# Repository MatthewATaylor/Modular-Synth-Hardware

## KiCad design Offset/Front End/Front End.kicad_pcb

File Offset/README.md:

# Offset

Two DC offsets, each applied to six output channels.

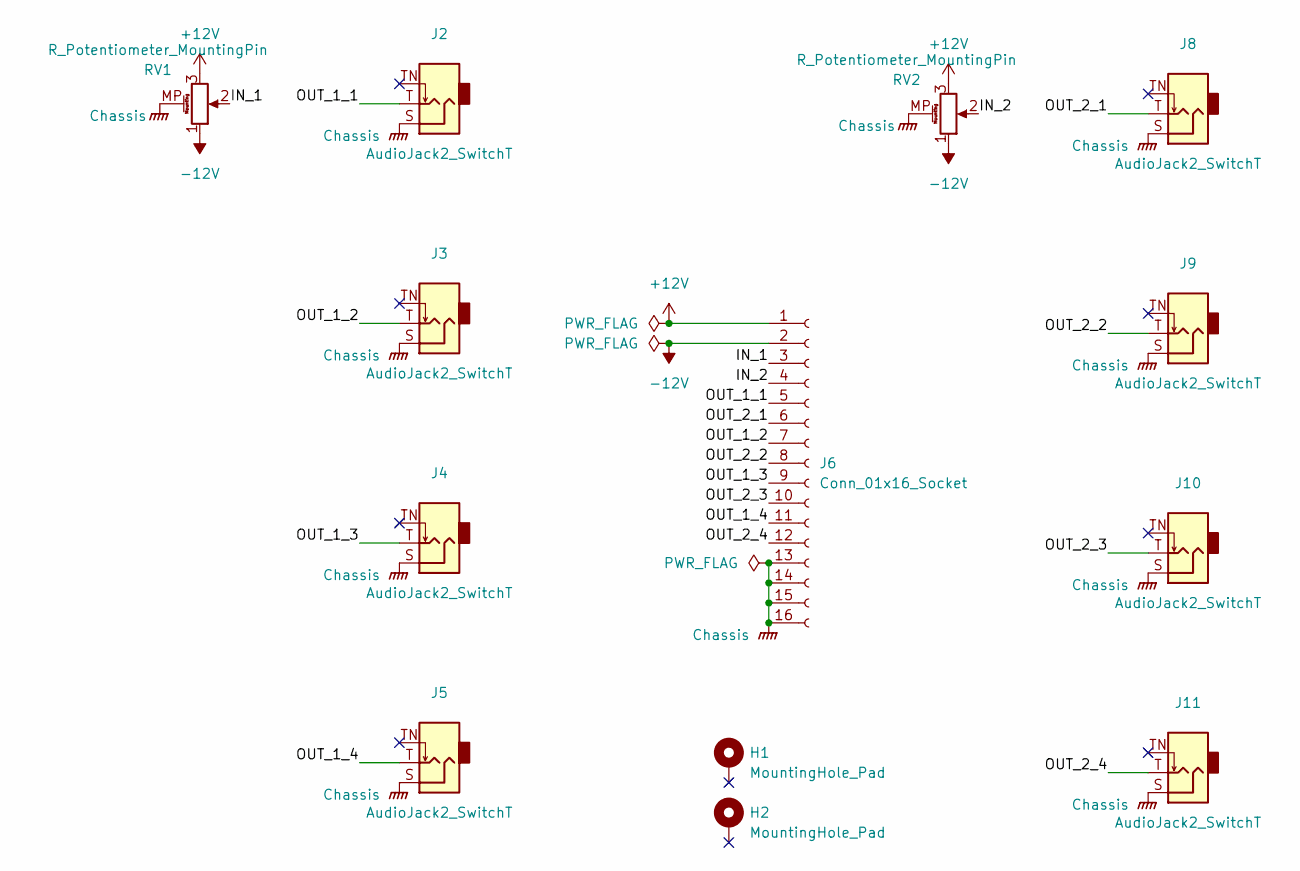
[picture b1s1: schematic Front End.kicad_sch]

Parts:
H1, H2: MountingHole_Pad; MountingHole_Pitch7.5mm_Drill3.4mm
J2, J3, J4, J5, J8, J9, J10, J11: AudioJack2_SwitchT; Jack_3.5mm_QingPu_WQP-PJ398SM_Vertical_CircularHoles
J6: Conn_01x16_Socket; PinSocket_1x16_P2.54mm_Vertical
RV1, RV2: R_Potentiometer_MountingPin; Potentiometer_Alpha_RD901F-40-00D_Single_Vertical_MP

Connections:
+12V: J6.1, RV1.3, RV2.3
-12V: J6.2, RV1.1, RV2.1
/IN_1: J6.3, RV1.2
/IN_2: J6.4, RV2.2
/OUT_1_1: J2.T, J6.5
/OUT_1_2: J3.T, J6.7
/OUT_1_3: J4.T, J6.9
/OUT_1_4: J5.T, J6.11
/OUT_2_1: J6.6, J8.T
/OUT_2_2: J6.8, J9.T
/OUT_2_3: J6.10, J10.T
/OUT_2_4: J6.12, J11.T
Chassis: J2.S, J3.S, J4.S, J5.S, J6.13, J6.14, J6.15, J6.16, J8.S, J9.S, J10.S, J11.S, RV1.MP (MountPin), RV2.MP (MountPin)

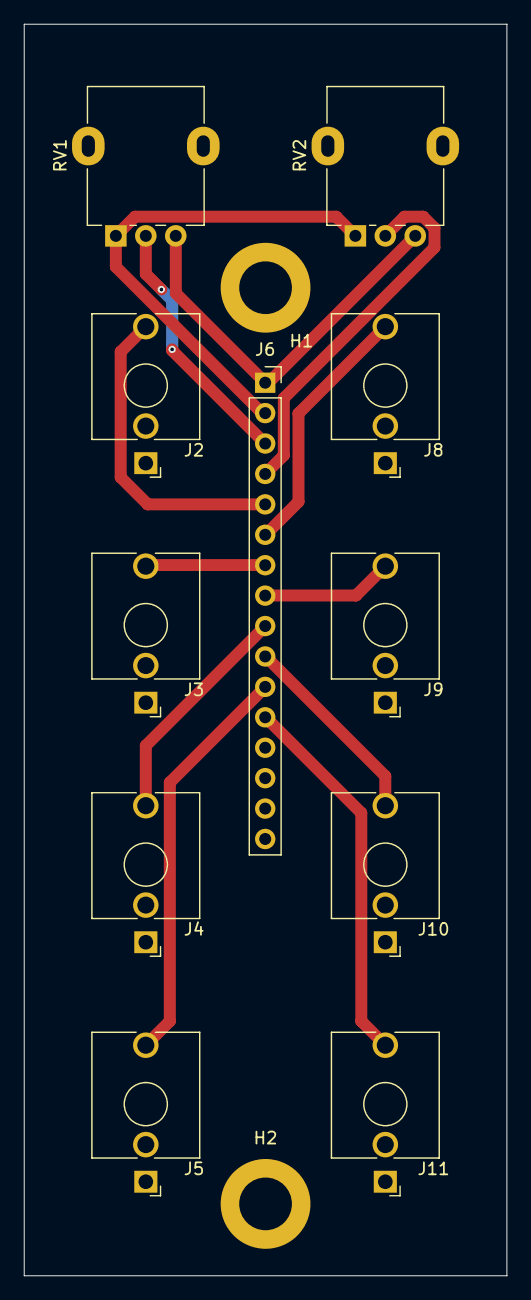
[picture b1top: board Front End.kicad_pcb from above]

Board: 2 copper layers, 40.3 x 104.5 mm, 13 parts (0 on the bottom side), 13 nets.

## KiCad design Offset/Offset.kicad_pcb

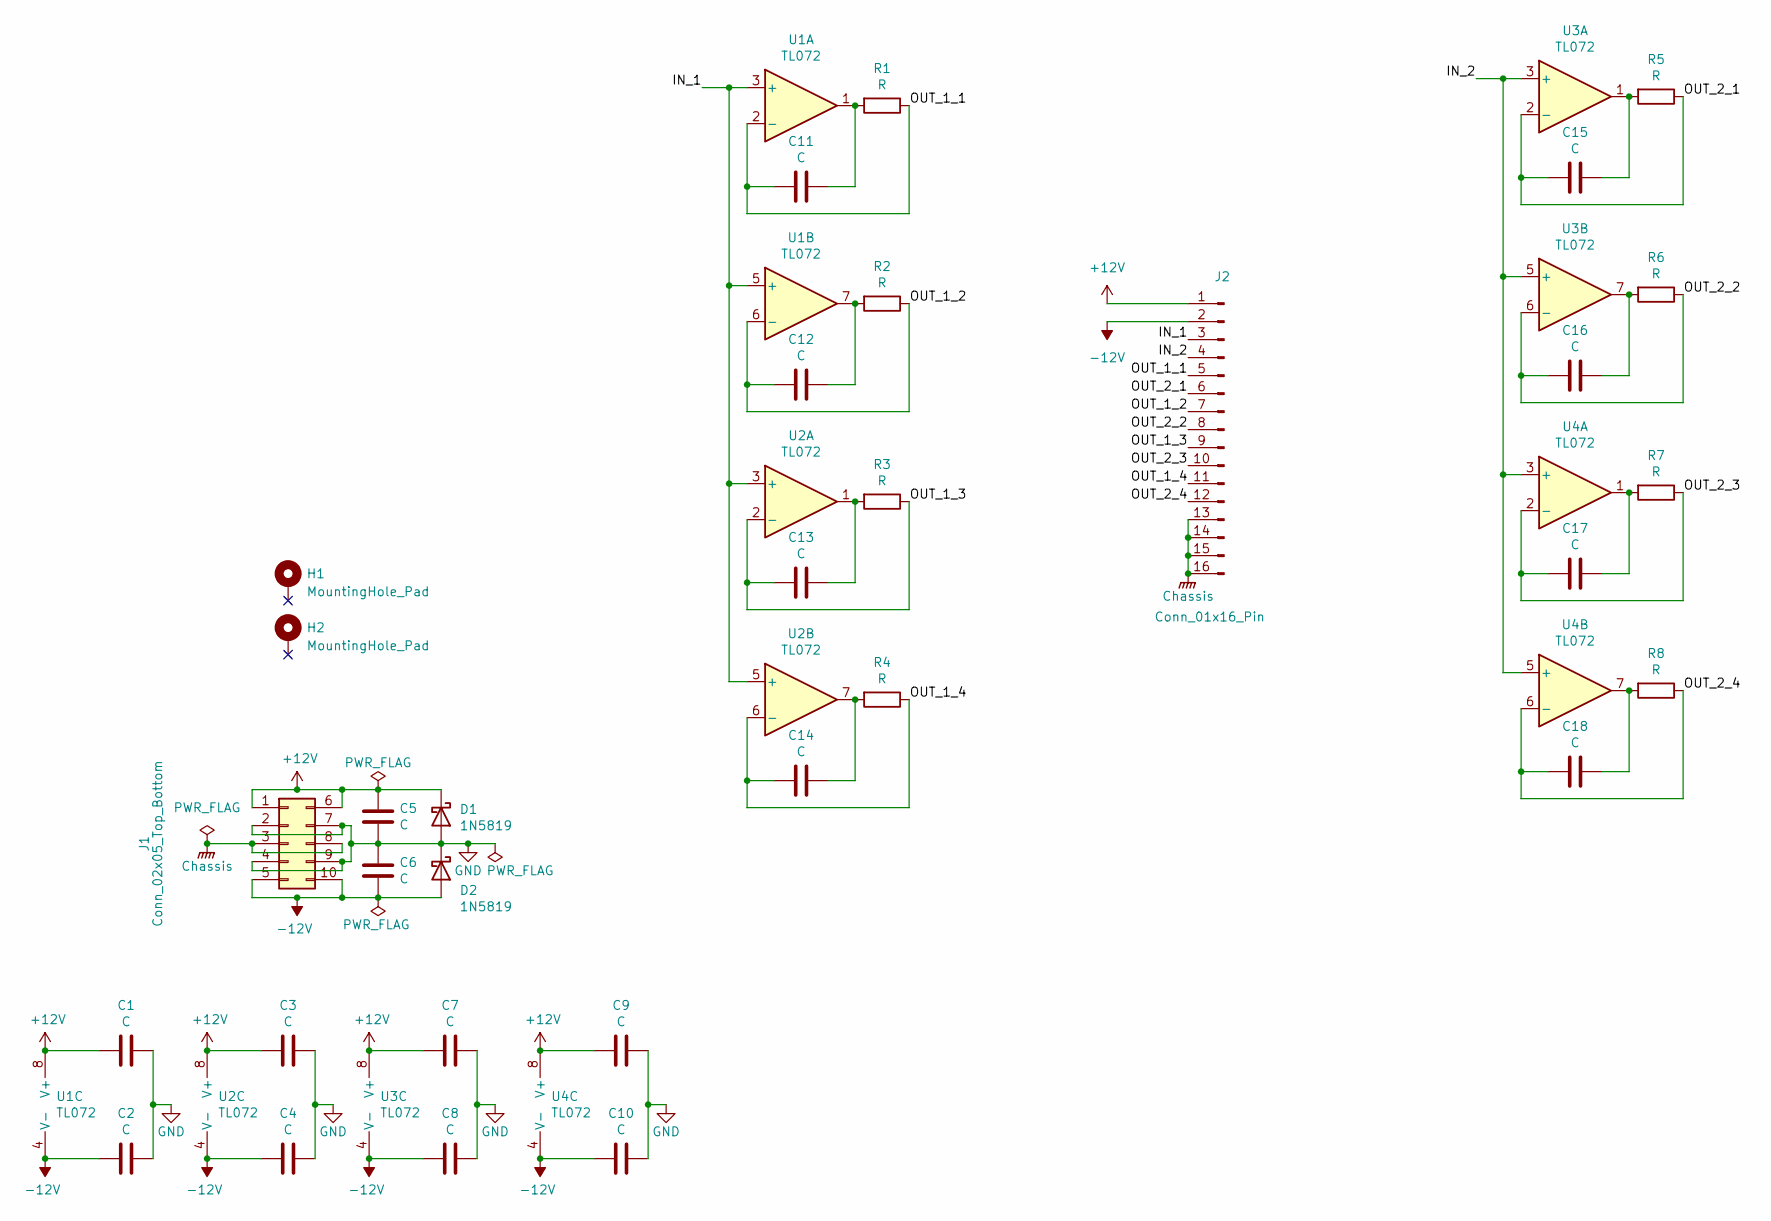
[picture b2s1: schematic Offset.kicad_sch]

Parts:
C1, C2, C3, C4, C7, C8, C9, C10, C11, C12, C13, C14, C15, C16, C17, C18: C; C_Disc_D5.5mm_W2.5mm_P2.50mm
C5, C6: C; C_Disc_D5.5mm_W4.0mm_P2.50mm
D1, D2: 1N5819; D_DO-41_SOD81_P10.16mm_Horizontal
H1, H2: MountingHole_Pad; MountingHole_Pitch7.5mm_Drill3.4mm
J1: Conn_02x05_Top_Bottom; Molex_Mini-Fit_Jr_5566-10A_2x05_P4.20mm_Vertical
J2: Conn_01x16_Pin; PinHeader_1x16_P2.54mm_Vertical
R1, R2, R3, R4, R5, R6, R7, R8: R; R_Axial_DIN0207_L6.3mm_D2.5mm_P7.62mm_Horizontal
U1, U2, U3, U4: TL072; DIP-8_W7.62mm_Socket

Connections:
+12V: C1.1, C3.1, C5.1, C7.1, C9.1, D1.1 (K), J1.1, J1.6, J2.1, U1.8 (V+), U2.8 (V+), U3.8 (V+), U4.8 (V+)
-12V: C2.1, C4.1, C6.2, C8.1, C10.1, D2.2 (A), J1.5, J1.10, J2.2, U1.4 (V-), U2.4 (V-), U3.4 (V-), U4.4 (V-)
/IN_1: J2.3, U1.3 (+), U1.5 (+), U2.3 (+), U2.5 (+)
/IN_2: J2.4, U3.3 (+), U3.5 (+), U4.3 (+), U4.5 (+)
/OUT_1_1: C11.1, J2.5, R1.1, U1.2 (-)
/OUT_1_2: C12.1, J2.7, R2.1, U1.6 (-)
/OUT_1_3: C13.1, J2.9, R3.1, U2.2 (-)
/OUT_1_4: C14.1, J2.11, R4.1, U2.6 (-)
/OUT_2_1: C15.1, J2.6, R5.1, U3.2 (-)
/OUT_2_2: C16.1, J2.8, R6.1, U3.6 (-)
/OUT_2_3: C17.1, J2.10, R7.1, U4.2 (-)
/OUT_2_4: C18.1, J2.12, R8.1, U4.6 (-)
Chassis: J1.3, J1.8, J2.13, J2.14, J2.15, J2.16
GND: C1.2, C2.2, C3.2, C4.2, C5.2, C6.1, C7.2, C8.2, C9.2, C10.2, D1.2 (A), D2.1 (K), J1.2, J1.4, J1.7, J1.9
unnamed: C11.2, R1.2, U1.1
unnamed: C12.2, R2.2, U1.7
unnamed: C13.2, R3.2, U2.1
unnamed: C14.2, R4.2, U2.7
unnamed: C15.2, R5.2, U3.1
unnamed: C16.2, R6.2, U3.7
unnamed: C17.2, R7.2, U4.1
unnamed: C18.2, R8.2, U4.7

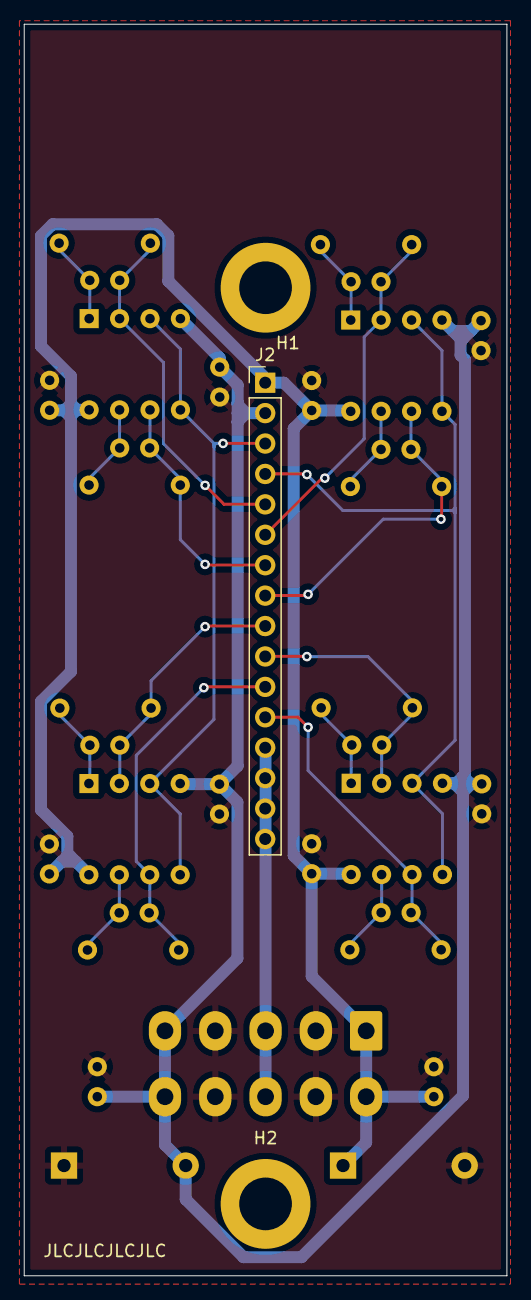
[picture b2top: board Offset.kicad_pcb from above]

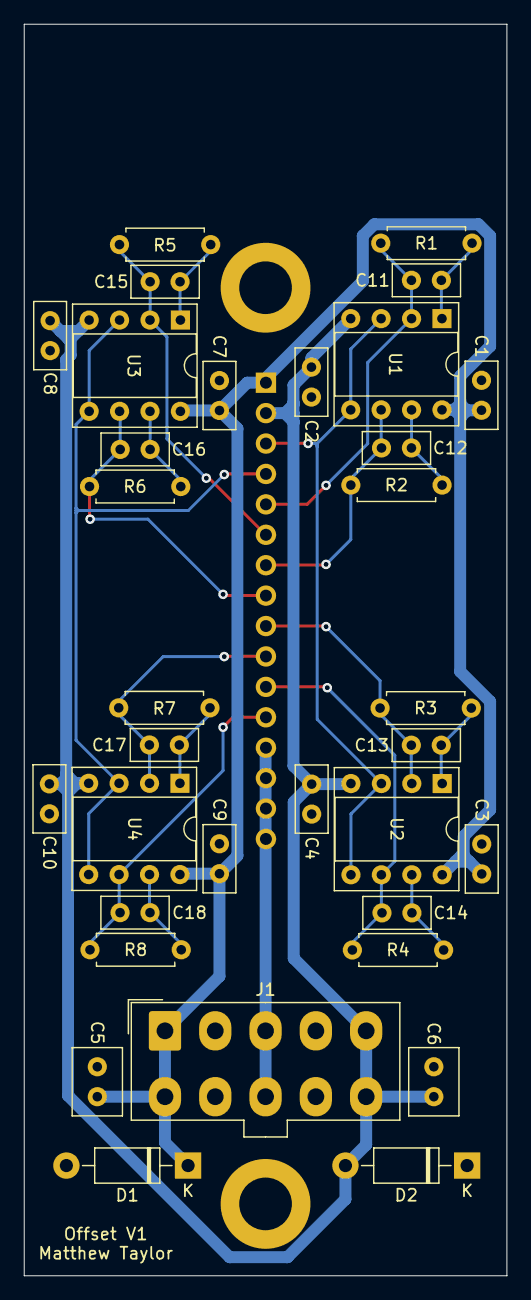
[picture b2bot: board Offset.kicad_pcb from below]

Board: 2 copper layers, 40.3 x 104.5 mm, 36 parts (33 on the bottom side), 22 nets.

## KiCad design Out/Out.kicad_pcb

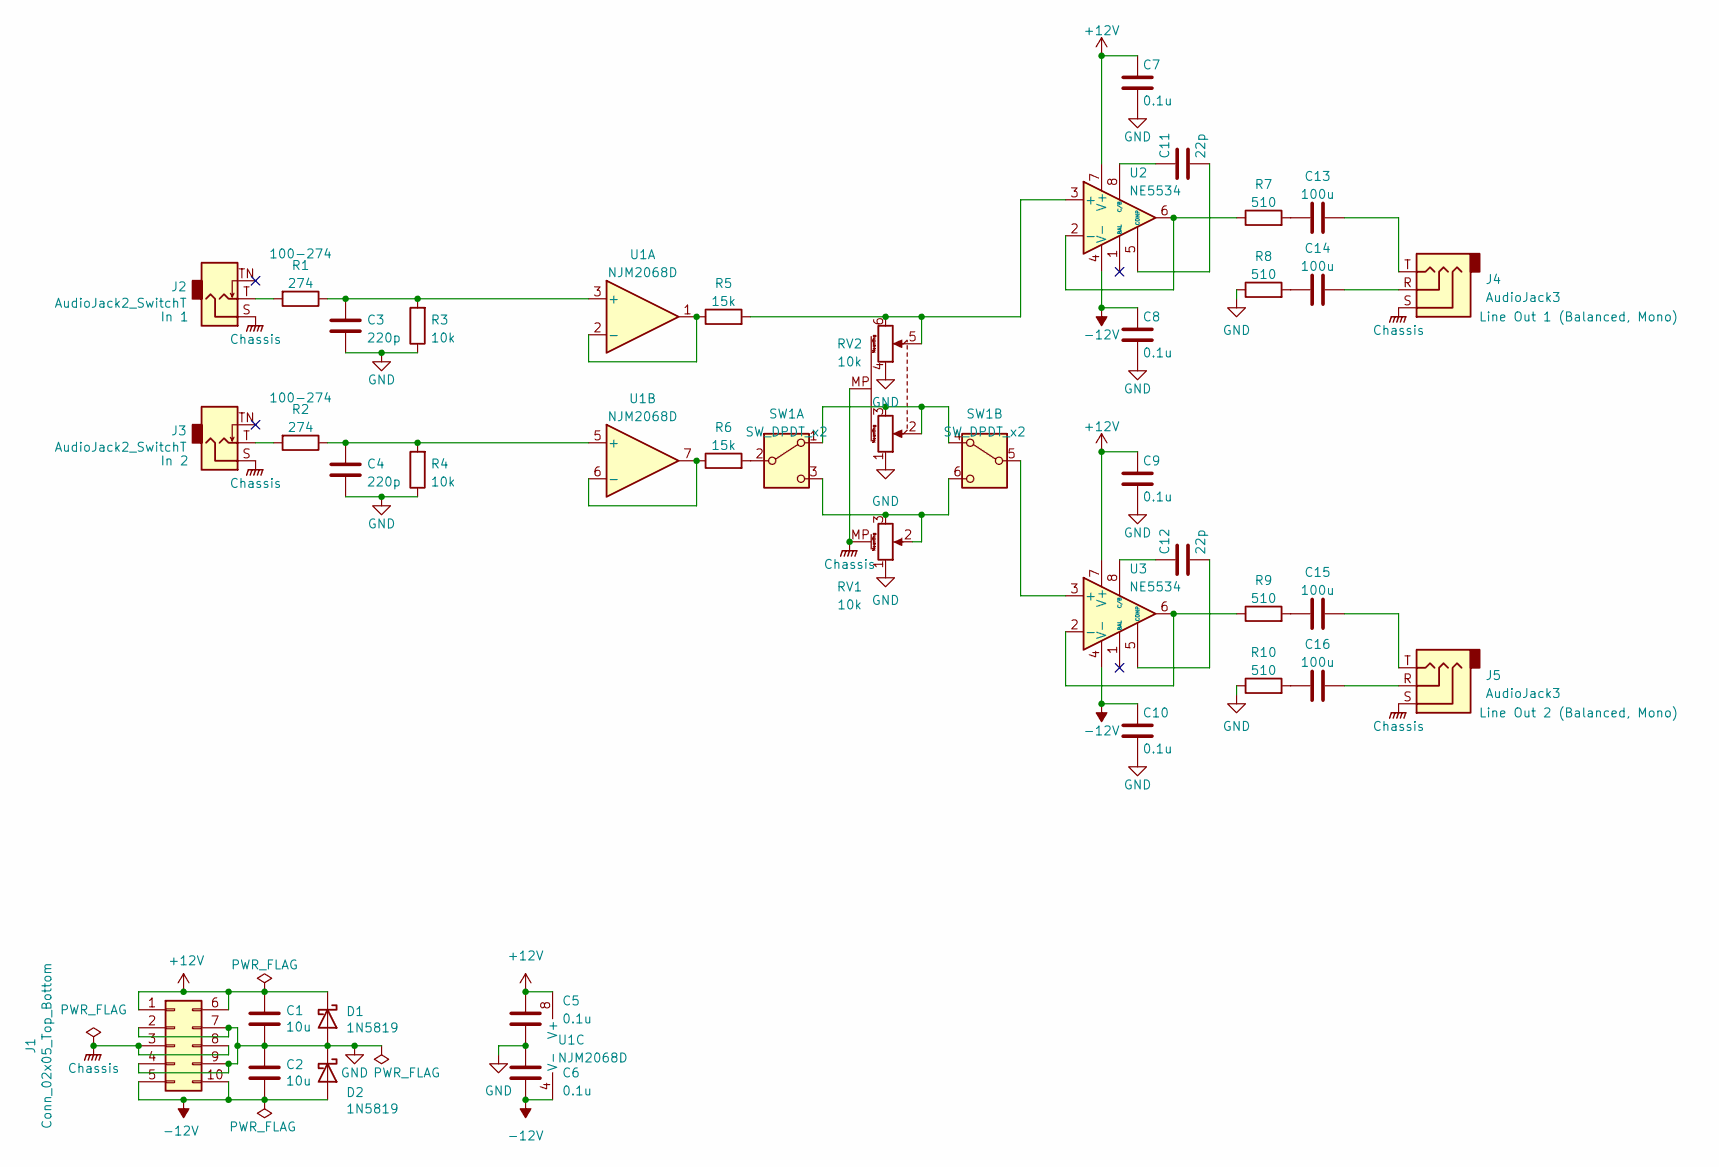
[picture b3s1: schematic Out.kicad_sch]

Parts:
C1, C2: 10u; C_Disc_D5.5mm_W4.0mm_P2.50mm
C3, C4: 220p; C_Disc_D5.5mm_W2.5mm_P2.50mm
C5, C6, C7, C8, C9, C10: 0.1u; C_Disc_D5.5mm_W2.5mm_P2.50mm
C11, C12: 22p; C_Disc_D5.5mm_W2.5mm_P2.50mm
C13, C14, C15, C16: 100u; C_Radial_D8.0mm_H11.5mm_P3.50mm
D1, D2: 1N5819; D_DO-41_SOD81_P10.16mm_Horizontal
J1: Conn_02x05_Top_Bottom; Molex_Mini-Fit_Jr_5566-10A_2x05_P4.20mm_Vertical
J2, J3: AudioJack2_SwitchT; Jack_3.5mm_QingPu_WQP-PJ398SM_Vertical_CircularHoles
J4, J5: AudioJack3; Jack_3.5mm_QingPu_WQP-PJ366ST_Vertical_CircularHoles
R1, R2: 274; R_Axial_DIN0207_L6.3mm_D2.5mm_P7.62mm_Horizontal
R3, R4: 10k; R_Axial_DIN0207_L6.3mm_D2.5mm_P7.62mm_Horizontal
R5, R6: 15k; R_Axial_DIN0207_L6.3mm_D2.5mm_P7.62mm_Horizontal
R7, R8, R9, R10: 510; R_Axial_DIN0207_L6.3mm_D2.5mm_P7.62mm_Horizontal
RV1: 10k; Potentiometer_Alpha_RD901F-40-00D_Single_Vertical_MP
RV2: 10k; Potentiometer_Alpha_RD902F-40-00D_Dual_Vertical
SW1: SW_DPDT_x2; MTS-202
U1: NJM2068D; DIP-8_W7.62mm_Socket
U2, U3: NE5534; SOIC-8_3.9x4.9mm_P1.27mm

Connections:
+12V: C1.1, C5.2, C7.1, C9.1, D1.1 (K), J1.1, J1.6, U1.8 (V+), U2.7 (V+), U3.7 (V+)
-12V: C2.2, C6.1, C8.1, C10.1, D2.2 (A), J1.5, J1.10, U1.4 (V-), U2.4 (V-), U3.4 (V-)
Chassis: J1.3, J1.8, J2.S, J3.S, J4.S, J5.S, RV1.MP (MountPin), RV2.MP (MountPin)
GND: C1.2, C2.1, C3.2, C4.2, C5.1, C6.2, C7.2, C8.2, C9.2, C10.2, D1.2 (A), D2.1 (K), J1.2, J1.4, J1.7, J1.9, R3.1, R4.1, R8.1, R10.1, RV1.1, RV2.1, RV2.4
unnamed: C13.1, R7.2
unnamed: C13.2, J4.T
unnamed: C14.1, R8.2
unnamed: C14.2, J4.R
unnamed: C15.1, R9.2
unnamed: C15.2, J5.T
unnamed: C16.1, R10.2
unnamed: C16.2, J5.R
unnamed: J2.T, R1.2
unnamed: J3.T, R2.2
unnamed: RV2.2, RV2.3, SW1.1 (A), SW1.4 (A)
unnamed: R6.2, SW1.2 (B)
unnamed: RV1.2, RV1.3, SW1.3 (C), SW1.6 (C)
unnamed: SW1.5 (B), U3.3 (+)
unnamed: C3.1, R1.1, R3.2, U1.3 (+)
unnamed: R5.1, U1.1, U1.2 (-)
unnamed: C4.1, R2.1, R4.2, U1.5 (+)
unnamed: R6.1, U1.6 (-), U1.7
unnamed: R5.2, RV2.5, RV2.6, U2.3 (+)
unnamed: R7.1, U2.2 (-), U2.6
unnamed: C11.2, U2.5 (COMP)
unnamed: C11.1, U2.8 (C/B)
unnamed: R9.1, U3.2 (-), U3.6
unnamed: C12.2, U3.5 (COMP)
unnamed: C12.1, U3.8 (C/B)

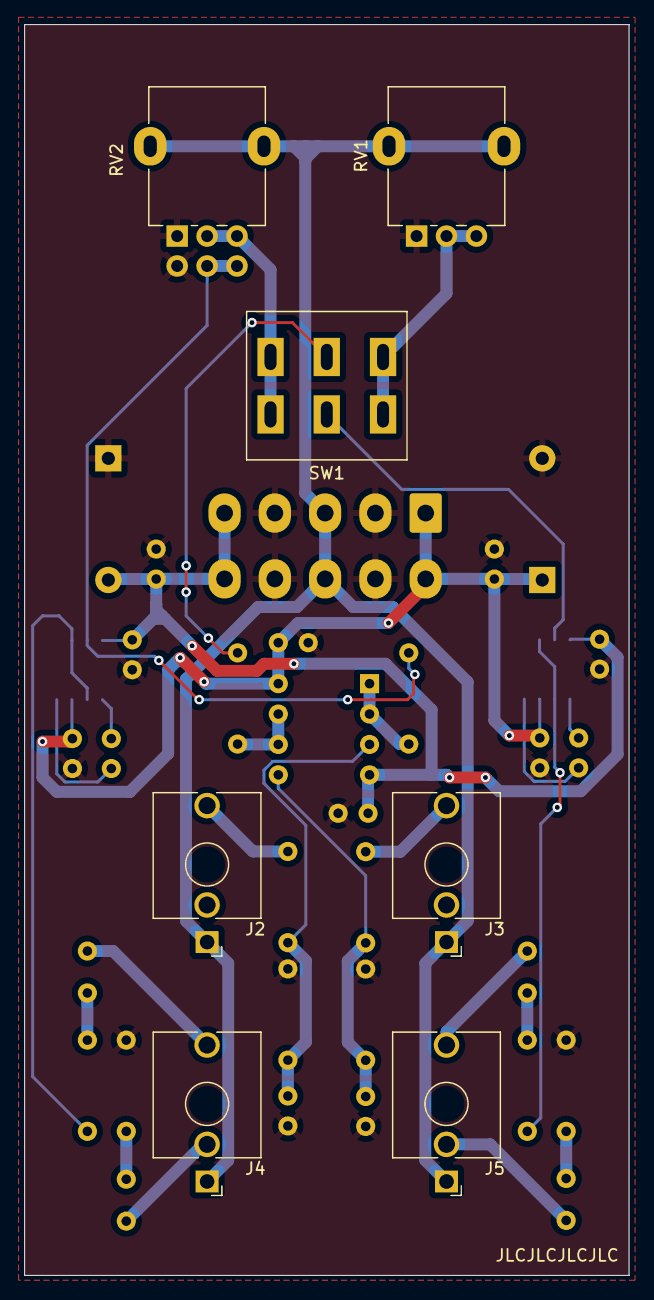
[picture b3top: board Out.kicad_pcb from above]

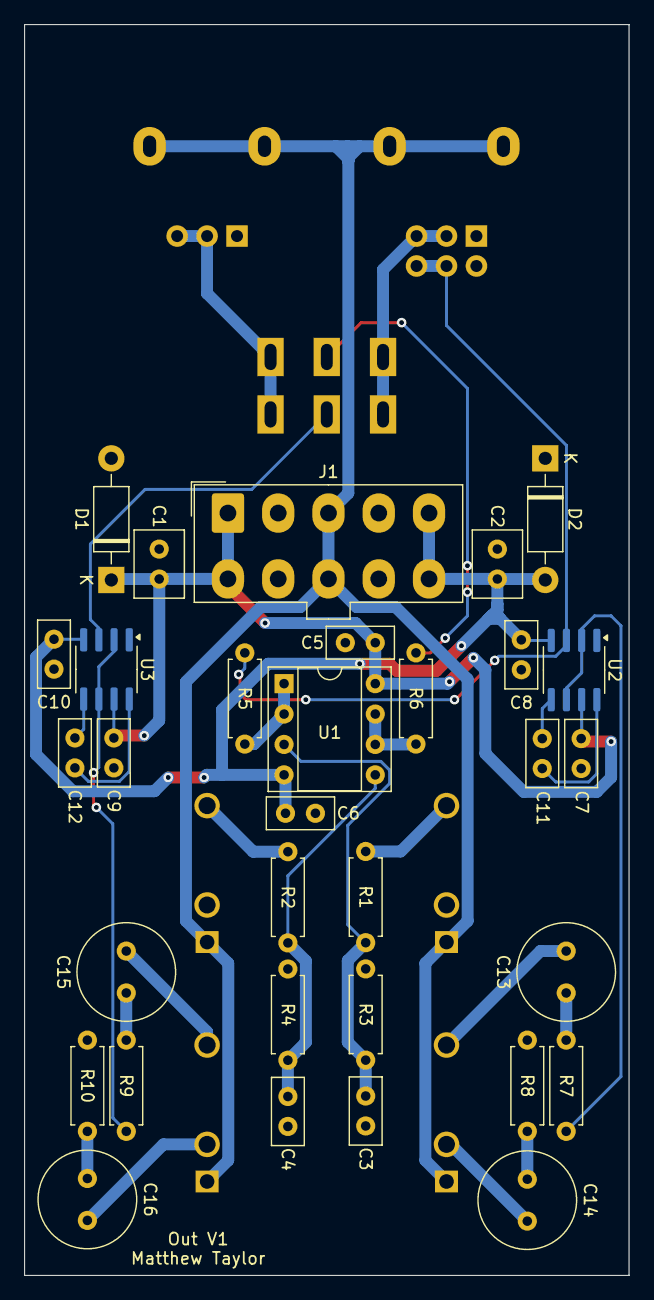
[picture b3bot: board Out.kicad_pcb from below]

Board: 2 copper layers, 50.5 x 104.5 mm, 39 parts (32 on the bottom side), 29 nets.

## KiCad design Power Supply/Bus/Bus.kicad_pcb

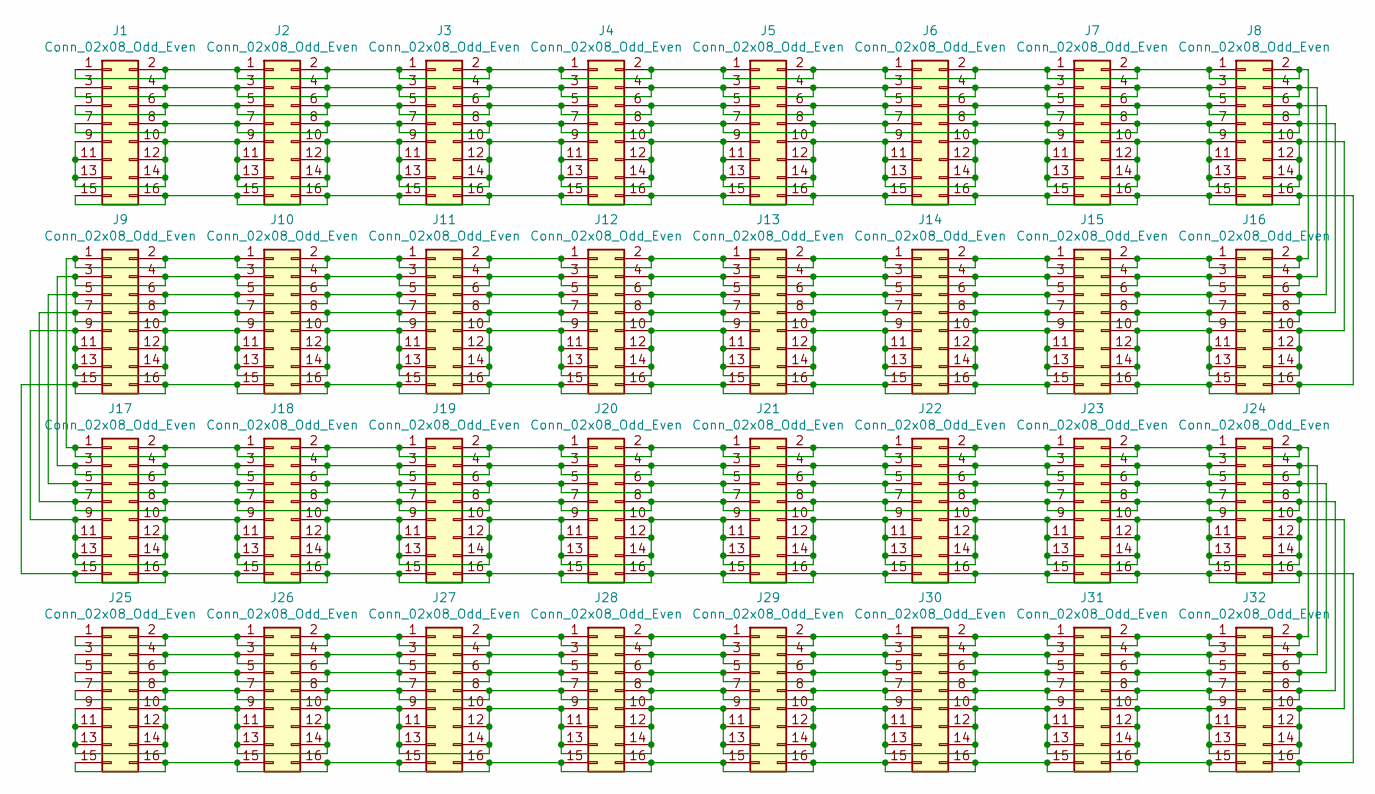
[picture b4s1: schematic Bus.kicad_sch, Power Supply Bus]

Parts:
J1, J2, J3, J4, J5, J6, J7, J8, J9, J10, J11, J12, J13, J14, J15, J16, J17, J18, J19, J20, J21, J22, J23, J24, J25, J26, J27, J28, J29, J30, J31, J32: Conn_02x08_Odd_Even; PinHeader_2x08_P2.54mm_Vertical

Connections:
unnamed: J1.1, J1.2, J2.1, J2.2, J3.1, J3.2, J4.1, J4.2, J5.1, J5.2, J6.1, J6.2, J7.1, J7.2, J8.1, J8.2, J9.1, J9.2, J10.1, J10.2, J11.1, J11.2, J12.1, J12.2, J13.1, J13.2, J14.1, J14.2, J15.1, J15.2, J16.1, J16.2, J17.1, J17.2, J18.1, J18.2, J19.1, J19.2, J20.1, J20.2, J21.1, J21.2, J22.1, J22.2, J23.1, J23.2, J24.1, J24.2, J25.1, J25.2, J26.1, J26.2, J27.1, J27.2, J28.1, J28.2, J29.1, J29.2, J30.1, J30.2, J31.1, J31.2, J32.1, J32.2
unnamed: J1.3, J1.4, J2.3, J2.4, J3.3, J3.4, J4.3, J4.4, J5.3, J5.4, J6.3, J6.4, J7.3, J7.4, J8.3, J8.4, J9.3, J9.4, J10.3, J10.4, J11.3, J11.4, J12.3, J12.4, J13.3, J13.4, J14.3, J14.4, J15.3, J15.4, J16.3, J16.4, J17.3, J17.4, J18.3, J18.4, J19.3, J19.4, J20.3, J20.4, J21.3, J21.4, J22.3, J22.4, J23.3, J23.4, J24.3, J24.4, J25.3, J25.4, J26.3, J26.4, J27.3, J27.4, J28.3, J28.4, J29.3, J29.4, J30.3, J30.4, J31.3, J31.4, J32.3, J32.4
unnamed: J1.5, J1.6, J2.5, J2.6, J3.5, J3.6, J4.5, J4.6, J5.5, J5.6, J6.5, J6.6, J7.5, J7.6, J8.5, J8.6, J9.5, J9.6, J10.5, J10.6, J11.5, J11.6, J12.5, J12.6, J13.5, J13.6, J14.5, J14.6, J15.5, J15.6, J16.5, J16.6, J17.5, J17.6, J18.5, J18.6, J19.5, J19.6, J20.5, J20.6, J21.5, J21.6, J22.5, J22.6, J23.5, J23.6, J24.5, J24.6, J25.5, J25.6, J26.5, J26.6, J27.5, J27.6, J28.5, J28.6, J29.5, J29.6, J30.5, J30.6, J31.5, J31.6, J32.5, J32.6
unnamed: J1.7, J1.8, J2.7, J2.8, J3.7, J3.8, J4.7, J4.8, J5.7, J5.8, J6.7, J6.8, J7.7, J7.8, J8.7, J8.8, J9.7, J9.8, J10.7, J10.8, J11.7, J11.8, J12.7, J12.8, J13.7, J13.8, J14.7, J14.8, J15.7, J15.8, J16.7, J16.8, J17.7, J17.8, J18.7, J18.8, J19.7, J19.8, J20.7, J20.8, J21.7, J21.8, J22.7, J22.8, J23.7, J23.8, J24.7, J24.8, J25.7, J25.8, J26.7, J26.8, J27.7, J27.8, J28.7, J28.8, J29.7, J29.8, J30.7, J30.8, J31.7, J31.8, J32.7, J32.8
unnamed: J1.9, J1.10, J1.11, J1.12, J1.13, J1.14, J2.9, J2.10, J2.11, J2.12, J2.13, J2.14, J3.9, J3.10, J3.11, J3.12, J3.13, J3.14, J4.9, J4.10, J4.11, J4.12, J4.13, J4.14, J5.9, J5.10, J5.11, J5.12, J5.13, J5.14, J6.9, J6.10, J6.11, J6.12, J6.13, J6.14, J7.9, J7.10, J7.11, J7.12, J7.13, J7.14, J8.9, J8.10, J8.11, J8.12, J8.13, J8.14, J9.9, J9.10, J9.11, J9.12, J9.13, J9.14, J10.9, J10.10, J10.11, J10.12, J10.13, J10.14, J11.9, J11.10, J11.11, J11.12, J11.13, J11.14, J12.9, J12.10, J12.11, J12.12, J12.13, J12.14, J13.9, J13.10, J13.11, J13.12, J13.13, J13.14, J14.9, J14.10, J14.11, J14.12, J14.13, J14.14, J15.9, J15.10, J15.11, J15.12, J15.13, J15.14, J16.9, J16.10, J16.11, J16.12, J16.13, J16.14, J17.9, J17.10, J17.11, J17.12, J17.13, J17.14, J18.9, J18.10, J18.11, J18.12, J18.13, J18.14, J19.9, J19.10, J19.11, J19.12, J19.13, J19.14, J20.9, J20.10, J20.11, J20.12, J20.13, J20.14, J21.9, J21.10, J21.11, J21.12, J21.13, J21.14, J22.9, J22.10, J22.11, J22.12, J22.13, J22.14, J23.9, J23.10, J23.11, J23.12, J23.13, J23.14, J24.9, J24.10, J24.11, J24.12, J24.13, J24.14, J25.9, J25.10, J25.11, J25.12, J25.13, J25.14, J26.9, J26.10, J26.11, J26.12, J26.13, J26.14, J27.9, J27.10, J27.11, J27.12, J27.13, J27.14, J28.9, J28.10, J28.11, J28.12, J28.13, J28.14, J29.9, J29.10, J29.11, J29.12, J29.13, J29.14, J30.9, J30.10, J30.11, J30.12, J30.13, J30.14, J31.9, J31.10, J31.11, J31.12, J31.13, J31.14, J32.9, J32.10, J32.11, J32.12, J32.13, J32.14
unnamed: J1.15, J1.16, J2.15, J2.16, J3.15, J3.16, J4.15, J4.16, J5.15, J5.16, J6.15, J6.16, J7.15, J7.16, J8.15, J8.16, J9.15, J9.16, J10.15, J10.16, J11.15, J11.16, J12.15, J12.16, J13.15, J13.16, J14.15, J14.16, J15.15, J15.16, J16.15, J16.16, J17.15, J17.16, J18.15, J18.16, J19.15, J19.16, J20.15, J20.16, J21.15, J21.16, J22.15, J22.16, J23.15, J23.16, J24.15, J24.16, J25.15, J25.16, J26.15, J26.16, J27.15, J27.16, J28.15, J28.16, J29.15, J29.16, J30.15, J30.16, J31.15, J31.16, J32.15, J32.16

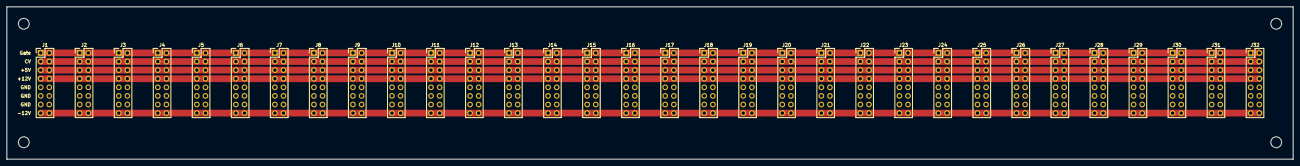
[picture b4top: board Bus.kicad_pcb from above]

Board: 2 copper layers, 380.0 x 45.0 mm, 32 parts (0 on the bottom side), 6 nets.
